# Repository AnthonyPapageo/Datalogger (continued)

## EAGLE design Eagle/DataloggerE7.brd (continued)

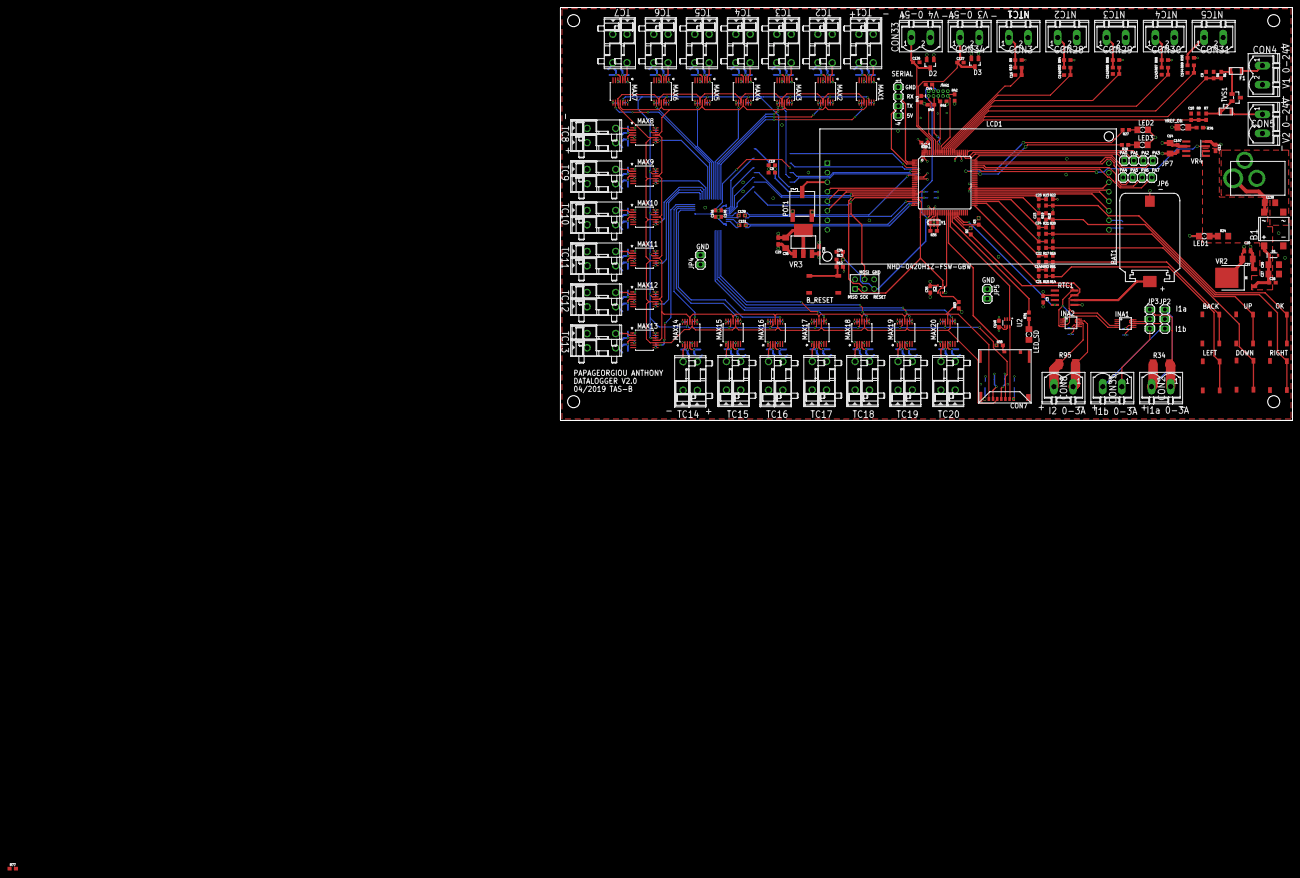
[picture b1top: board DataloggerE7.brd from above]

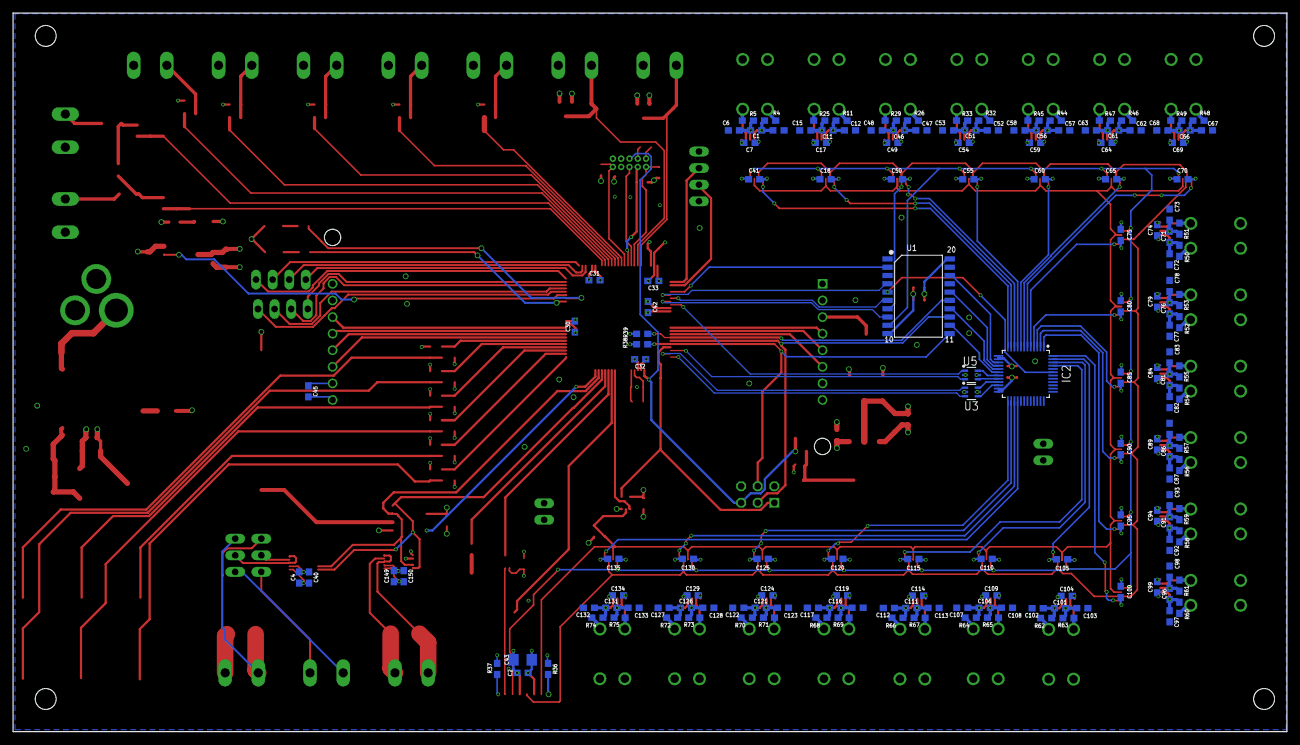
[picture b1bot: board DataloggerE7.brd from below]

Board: 4 copper layers, 195.0 x 110.0 mm, 339 parts (160 on the bottom side), 214 nets.

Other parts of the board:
R77: 10k; 0603

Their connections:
3V3: R77.1; also elsewhere on the board
CS_MAX1: R77.2; also elsewhere on the board

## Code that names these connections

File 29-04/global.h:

#ifndef GLOBAL_H
#define GLOBAL_H

#include <avr/eeprom.h>

#include <stdint.h>
#include <LiquidCrystal.h>
#include <LiquidMenu.h>
#include <INA.h>
#include <RTClib.h>
#include "MAX31856.h"

#define MAX_TC_NB 20
#define MAX_NTC_NB 5
#define MAX_V24_NB 2
#define MAX_V5_NB 2
#define MAX_I_NB 4


//OBJECT
extern INA_Class INA;
extern RTC_DS3231 RTC;
extern LiquidScreen* current_screen;//Used so we have to call get_currentScreen only once
extern LiquidScreen* previous_screen;
extern MAX31856 max_array[20];

////////MEASURE///////////
extern float TC_Measure_Array[MAX_TC_NB ];
extern float NTC_Measure_Array[MAX_NTC_NB];
extern float V24_Measure_Array[MAX_V24_NB];
extern float V5_Measure_Array[MAX_V5_NB];
extern int32_t I_Measure_Array[MAX_I_NB];//contain bus voltage and current


/////////EEPROM DATA///////////
extern uint8_t EEMEM NV_NTC_nb;
extern uint8_t EEMEM NV_TC_nb;
extern uint8_t EEMEM NV_I_nb;
extern uint8_t EEMEM NV_V24_nb;
extern uint8_t EEMEM NV_V5_nb;
extern float EEMEM  NV_B_FACTOR;
extern float EEMEM NV_R_25;
extern uint8_t EEMEM NV_IntervalSeconds;
extern uint8_t EEMEM NV_IntervalMinutes;
extern uint16_t EEMEM NV_R_SHUNT;

/////////NUMBER OF DEVICES ///////////
extern uint8_t NTC_nb;
extern uint8_t TC_nb;
extern uint8_t I_nb;
extern uint8_t V24_nb;
extern uint8_t V5_nb;


/////////INTERVAL///////////
extern uint8_t IntervalSeconds;
extern uint8_t IntervalMinutes;

//////////////LCD//////////////
extern const uint8_t RS;
extern const uint8_t RW;
extern const uint8_t ENABLE_LCD;
extern const uint8_t D4;
extern const uint8_t D5;
extern const uint8_t D6;
extern const uint8_t D7;
extern const uint8_t LCD_COL;
extern const uint8_t LCD_ROWS;


//////////////SPI//////////////
extern const uint32_t SPI_SPEED;

//////////////I2C//////////////
extern const uint32_t I2C_SPEED;

//////////////MUX//////////////
extern const uint8_t CS_MAX1;
extern const uint8_t CS_MAX2;
extern const uint8_t CS_MAX3;
extern const uint8_t CS_MAX4;
extern const uint8_t CS_MAX5;
extern const uint8_t CS_MAX6;
extern const uint8_t CS_MAX7;
extern const uint8_t CS_MAX8;
extern const uint8_t CS_MAX9;
extern const uint8_t CS_MAX10;
extern const uint8_t CS_MAX11;
extern const uint8_t CS_MAX12;
extern const uint8_t CS_MAX13;
extern const uint8_t CS_MAX14;
extern const uint8_t CS_MAX15;
extern const uint8_t CS_MAX16;
extern const uint8_t CS_MAX17;
extern const uint8_t CS_MAX18;
extern const uint8_t CS_MAX19;
extern const uint8_t CS_MAX20;
extern const uint8_t CS_SD;
extern const uint8_t CS_DISABLE;


//////////////NTC//////////////
extern float B_FACTOR;
extern float R_25;
extern const float R_LINE_NTC;
extern const float V_SUPPLY;

//////////////0-24V READINGS//////////////
extern const float R_UP;
extern const float R_DOWN;



//////////////CURRENT SENSING//////////////
extern uint16_t R_SHUNT;
extern const uint16_t DEFAULT_R_SHUNT;


/////////GLYPH///////////
namespace GLYPH
{
	extern uint8_t upArrow[8];
	extern uint8_t downArrow[8];
	extern uint8_t rightArrow[8];
	extern uint8_t leftArrow[8];
	extern const uint8_t upArrowIndex;
	extern const uint8_t downArrowIndex;
	extern const uint8_t rightArrowIndex;
	extern const uint8_t leftArrowIndex;
}

/*namespace ADCChannel
{
	extern const uint8_t V1;
	extern const uint8_t V2;
	extern const uint8_t V3;
	extern const uint8_t V4;
	extern const uint8_t NTC1;
	extern const uint8_t NTC2;
	extern const uint8_t NTC3;
	extern const uint8_t NTC4;
	extern const uint8_t NTC5;
}*/
extern const uint8_t NTCChannel[5];

 
#endif

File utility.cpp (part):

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{
	DDRE |= (1 << 3) | (1 << 4) | (1 << 5) | (1 << 6) | (1 << 7); //MUX address data as output
	DDRB |= (1 << 0) | (1 << 4) | (1 << 5) | (1 << 6);//SS , !CS_MUX, !EN_MUX, !WR_MUX as output
	PORTB |= (1 << 5); //!WR_MUX = 1
	PORTB &= ~(1 << 4); //!CS_MUX = 0
	PORTB &= ~(1 << 6); //!EN_MUX = 0 
	DDRL |= (1 << 4); //OEBUF as output
	PORTL |= (1 << 4); //OEBUF = 1, enable output of 3v3 to 5V buffer
	
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
void setMux(const uint8_t value)
{
	PORTE &= 0x07; //clear PE3 to PE7
	if (value < 20)
	{
		PORTB &= ~(1 << 0); //SS = 0
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
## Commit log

2019-04-27 Library
2019-04-29 29-04
2019-04-30 Add save to SD
2019-05-07 Todo back button
2019-05-08 Interrupt
2019-05-09 test static
2019-05-10 Max Opti
2019-05-10 done chenillard
2019-05-13 ISR timer
2019-05-17 correction bug ADC
2019-05-17 compare
2019-05-21 SD correction and SD for proto
2019-05-24 Final proto
2019-06-06 Final realease
2019-06-06 Add measures
2019-06-06 Add Eagle
2019-06-06 update include
2019-06-06 updated include
2019-06-06 updated main
2019-06-16 Create LICENSE
